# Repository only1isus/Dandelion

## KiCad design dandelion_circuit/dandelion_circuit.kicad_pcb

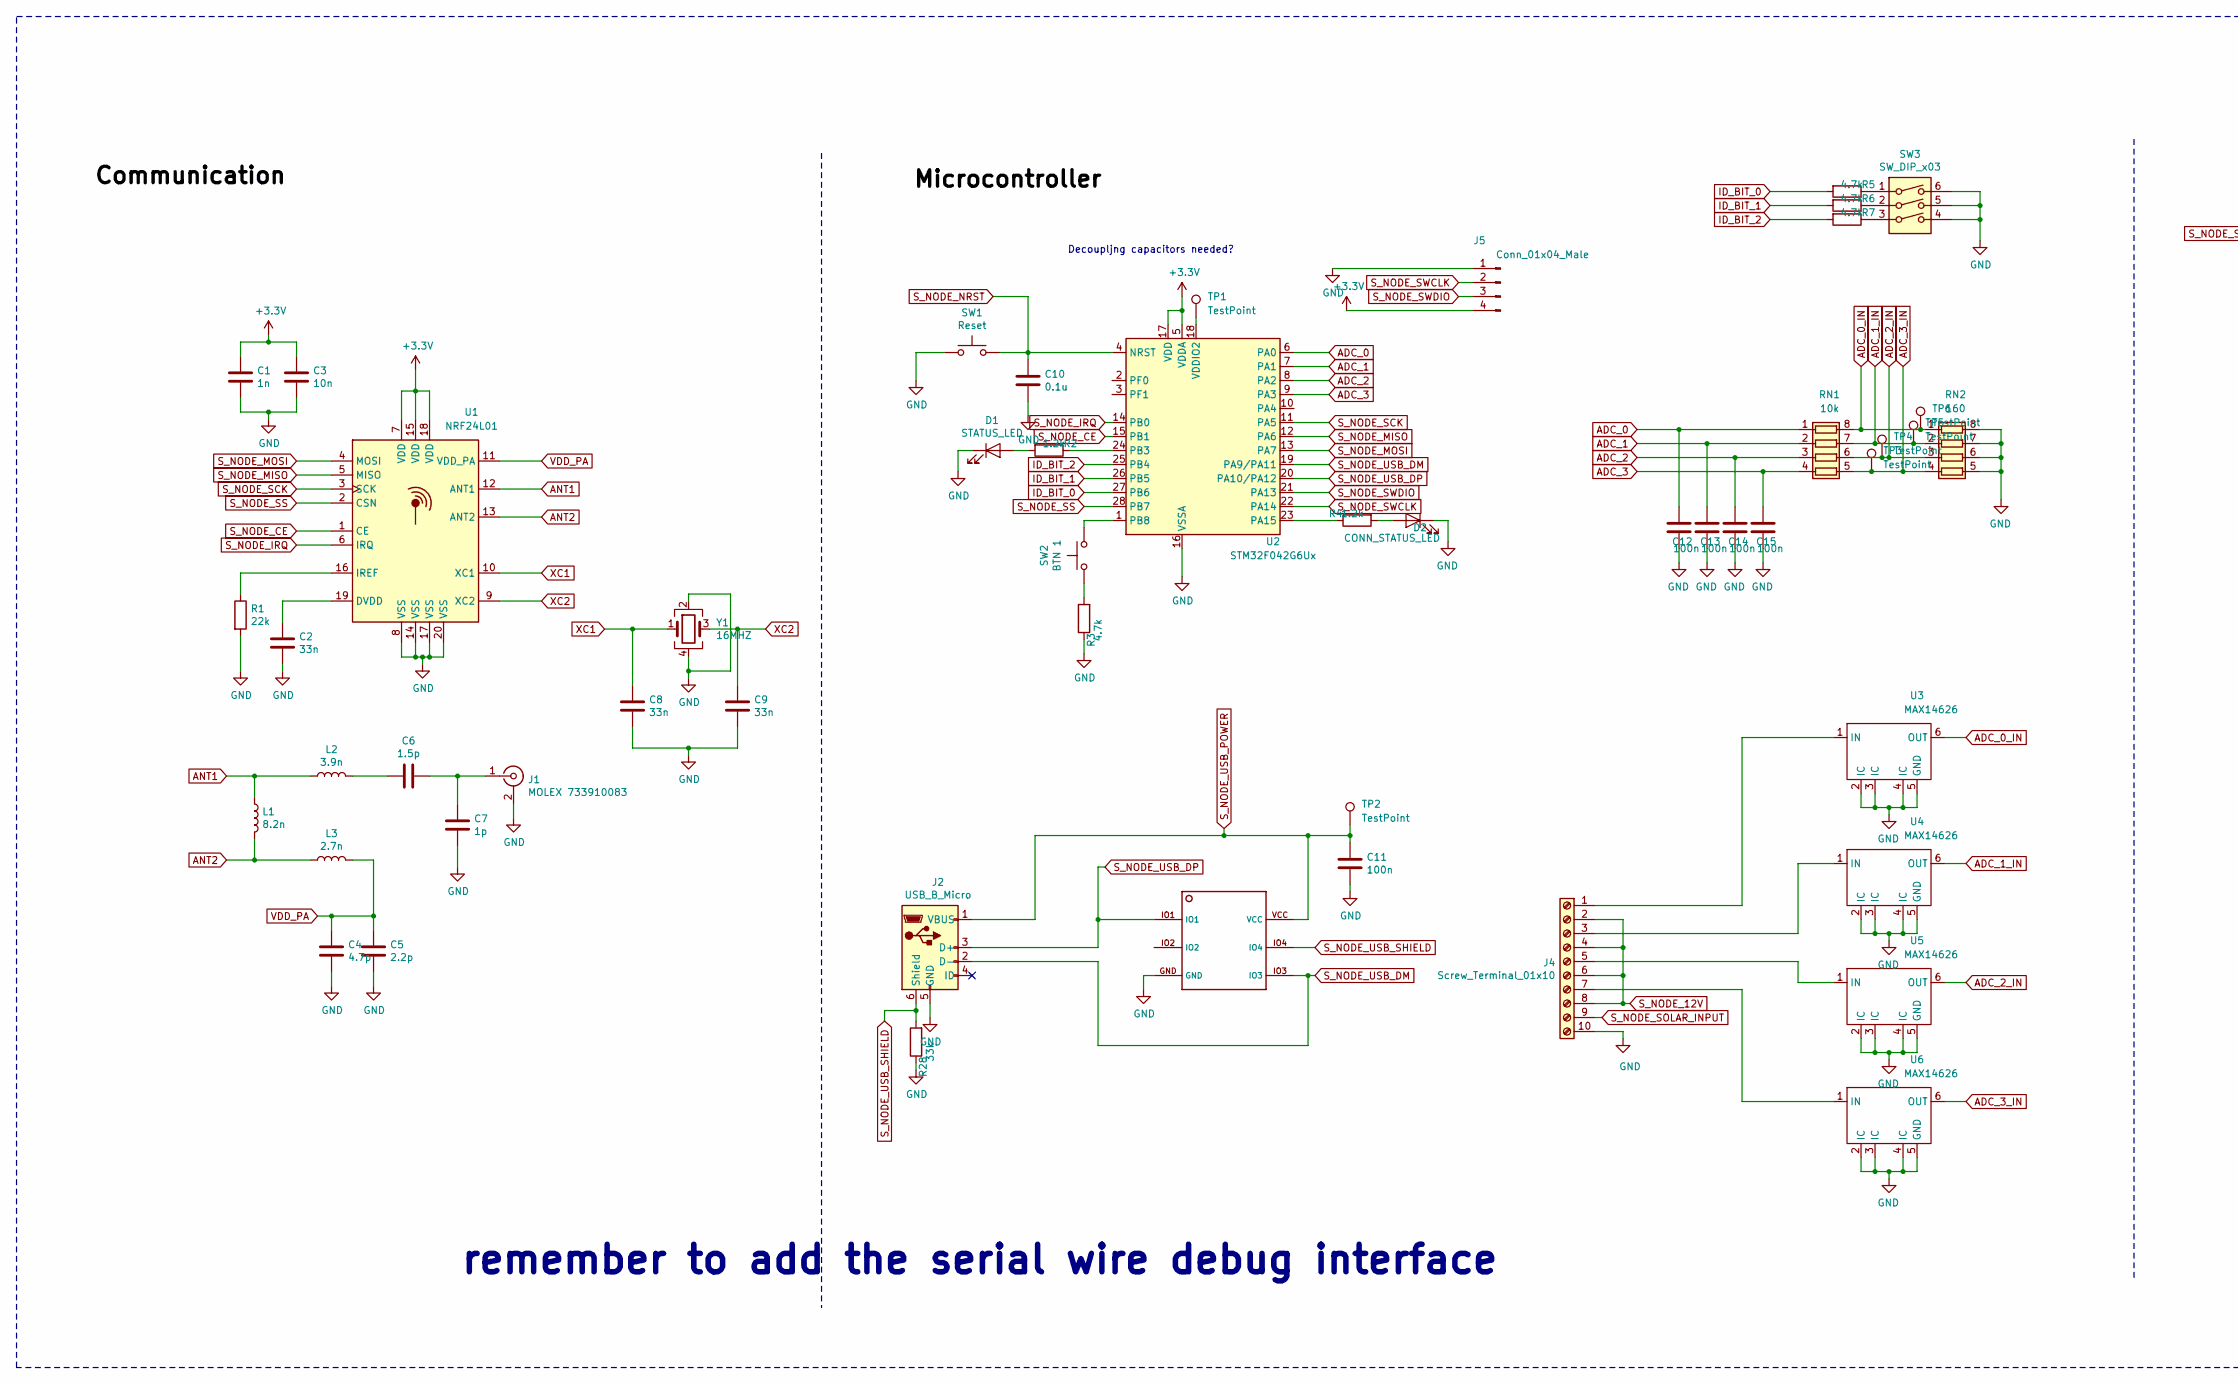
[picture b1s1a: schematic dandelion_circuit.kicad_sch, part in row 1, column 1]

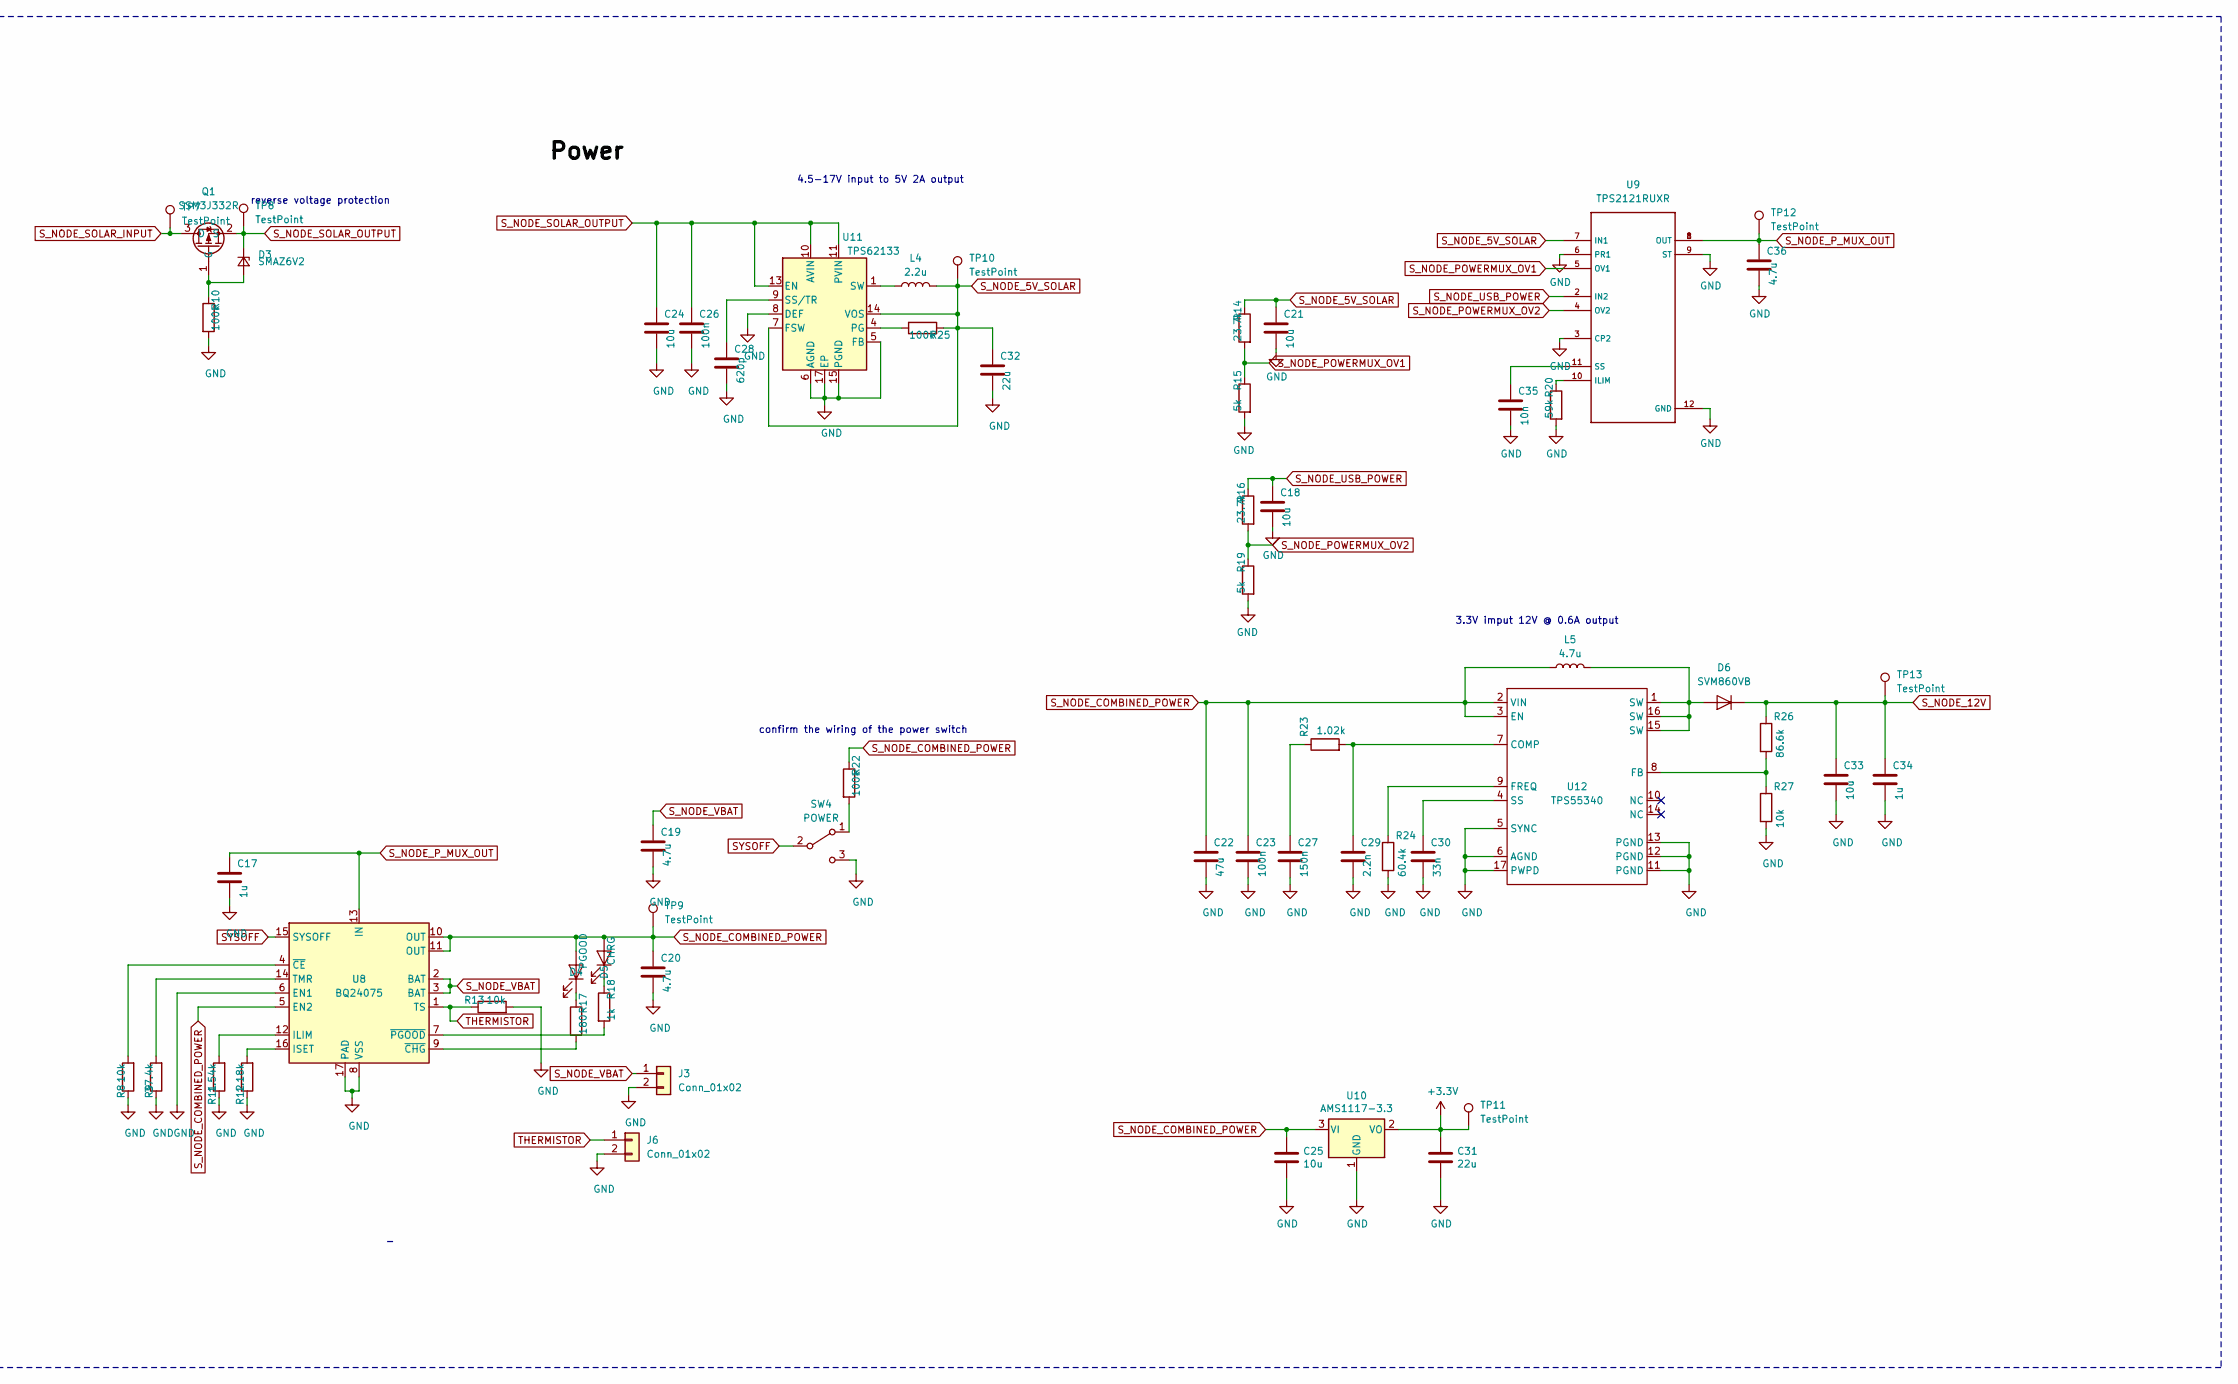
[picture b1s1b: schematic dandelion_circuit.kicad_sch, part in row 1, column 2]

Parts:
C1: 1n; C_0402_1005Metric
C2, C8, C9, C30: 33n; C_0402_1005Metric
C3, C35: 10n; C_0402_1005Metric
C4: 4.7p; C_0402_1005Metric
C5: 2.2p; C_0402_1005Metric
C6: 1.5p; C_0402_1005Metric
C7: 1p; C_0402_1005Metric
C10: 0.1u; C_0402_1005Metric
C11, C12, C13, C14, C15, C23, C26: 100n; C_0402_1005Metric
C17, C34: 1u; C_0402_1005Metric
C18, C24: 10u; C_0805_2012Metric
C19, C20: 4.7u; C_0402_1005Metric
C21, C25, C33: 10u; C_0402_1005Metric
C22: 47u; C_0402_1005Metric
C27: 150n; C_0402_1005Metric
C28: 620p; C_0402_1005Metric
C29: 2.2n; C_0402_1005Metric
C31, C32: 22u; C_0402_1005Metric
C36: 4.7u; C_0805_2012Metric
D1: STATUS_LED; LED_0805_2012Metric
D2: CONN_STATUS_LED; LED_0805_2012Metric
D3: SMAZ6V2; D_SMA
D4: PGOOD; LED_0805_2012Metric
D5: CHRG; LED_0805_2012Metric
D6: SVM860VB; TO-277B
J1: MOLEX 733910083; U.FL_Molex_MCRF_73412-0110_Vertical
J2: USB_B_Micro; USB_Micro-B_Molex-105133-0031
J3, J6: Conn_01x02; PinHeader_1x02_P2.00mm_Vertical
J4: Screw_Terminal_01x10; Connector_Phoenix_MKKDSN
J5: Conn_01x04_Male; PinHeader_1x04_P1.27mm_Vertical
L1: 8.2n; L_0402_1005Metric
L2: 3.9n; L_0402_1005Metric
L3: 2.7n; L_0402_1005Metric
L4: 2.2u; Inductor_Sunlord_MWSA0603
L5: 4.7u; Sunlord_MWSA0503S
Q1: SSM3J332R; SOT-23
R1: 22k; R_0402_1005Metric
R2, R4: 1.2k; R_0402_1005Metric
R3, R5, R6, R7: 4.7k; R_0402_1005Metric
R8, R13, R27: 10k; R_0402_1005Metric
R9: 37.4k; R_0402_1005Metric
R10: 100k; R_0603_1608Metric
R11: 1.54k; R_0603_1608Metric
R12: 1.18k; R_0603_1608Metric
R14, R16: 23.7k; R_0402_1005Metric
R15, R19: 5k; R_0402_1005Metric
R17: 180; R_0402_1005Metric
R18: 1k; R_0402_1005Metric
R20: 59k; R_0402_1005Metric
R22, R25: 100k; R_0402_1005Metric
R23: 1.02k; R_0402_1005Metric
R24: 60.4k; R_0402_1005Metric
R26: 86.6k; R_0402_1005Metric
R28: 33k; R_0402_1005Metric
RN1: 10k; R_Array_Convex_4x0603
RN2: 160; R_Array_Convex_4x0603
SW1: Reset; SW_Push_1P1T_NO_Vertical_Wuerth_434133025816
SW2: BTN 1; SW_Push_1P1T_NO_Vertical_Wuerth_434133025816
SW3: SW_DIP_x03; SW_DIP_SPSTx03_Slide_KingTek_DSHP03TJ_W5.25mm_P1.27mm_JPin
SW4: POWER; SW_SPDT_PCM12
TP1, TP2, TP3, TP4, TP5, TP6, TP7, TP8, TP9, TP10, TP11, TP12, TP13: TestPoint; TestPoint_Pad_2.0x2.0mm
U1: NRF24L01; QFN-20-1EP_4x4mm_P0.5mm_EP2.5x2.5mm
U2: STM32F042G6Ux; QFN-28_4x4mm_P0.5mm
U3, U4, U5, U6: MAX14626; DFN-6-1EP_3x3mm_P1mm_EP1.5x2.4mm
U8: BQ24075; VQFN-16-1EP_3x3mm_P0.5mm_EP1.68x1.68mm_ThermalVias
U9: TPS2121RUXR; IC_TPS2121RUXR
U10: AMS1117-3.3; SOT-223-3_TabPin2
U11: TPS62133; VQFN-16-1EP_3x3mm_P0.5mm_EP1.68x1.68mm_ThermalVias
U12: TPS55340; QFN50P300X300X80-17N
U13: TPD4E004DRYR; SON-6
Y1: 16MHZ; Crystal_SMD_Abracon_ABM10-4Pin_2.5x2.0mm

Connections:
+3V3: C1.1, C3.1, C31.1, J5.4, TP11.1, U1.7 (VDD), U1.15 (VDD), U1.18 (VDD), U2.5 (VDDA), U2.17 (VDD), U10.2 (VO)
ADC_0: C12.1, RN1.1 (R1.1), U2.6 (PA0)
ADC_0_IN: RN1.8 (R1.2), RN2.1 (R1.1), TP6.1, U3.6 (OUT)
ADC_1: C13.1, RN1.2 (R2.1), U2.7 (PA1)
ADC_1_IN: RN1.7 (R2.2), RN2.2 (R2.1), TP5.1, U4.6 (OUT)
ADC_2: C14.1, RN1.3 (R3.1), U2.8 (PA2)
ADC_2_IN: RN1.6 (R3.2), RN2.3 (R3.1), TP4.1, U5.6 (OUT)
ADC_3: C15.1, RN1.4 (R4.1), U2.9 (PA3)
ADC_3_IN: RN1.5 (R4.2), RN2.4 (R4.1), TP3.1, U6.6 (OUT)
ANT1: L1.1, L2.1, U1.12 (ANT1)
ANT2: L1.2, L3.1, U1.13 (ANT2)
GND: C1.2, C2.2, C3.2, C4.2, C5.2, C7.2, C8.2, C9.2, C10.2, C11.2, C12.2, C13.2, C14.2, C15.2, C17.2, C18.2, C19.2, C20.2, C21.2, C22.2, C23.2, C24.2, C25.2, C26.2, C27.2, C28.2, C29.2, C30.2, C31.2, C32.2, C33.2, C34.2, C35.2, C36.2, D1.1 (K), D2.1 (K), J1.2 (Ext), J2.5 (GND), J3.2, J4.10, J5.1, J6.2, R1.2, R3.1, R8.1, R9.1, R10.2, R11.1, R12.1, R13.2, R15.2, R19.2, R20.2, R24.2, R27.2, R28.1, RN2.5 (R4.2), RN2.6 (R3.2), RN2.7 (R2.2), RN2.8 (R1.2), SW1.1, SW3.4, SW3.5, SW3.6, SW4.3 (C), U1.8 (VSS), U1.14 (VSS), U1.17 (VSS), U1.20 (VSS), U2.16 (VSSA), U3.2 (IC), U3.3 (IC), U3.4 (IC), U3.5 (GND), U4.2 (IC), U4.3 (IC), U4.4 (IC), U4.5 (GND), U5.2 (IC), U5.3 (IC), U5.4 (IC), U5.5 (GND), U6.2 (IC), U6.3 (IC), U6.4 (IC), U6.5 (GND), U8.6 (EN1), U8.8 (VSS), U8.17 (PAD), U9.3 (CP2), U9.6 (PR1), U9.9 (ST), U9.12 (GND), U10.1 (GND), U11.5 (FB), U11.6 (AGND), U11.8 (DEF), U11.15 (PGND), U11.16 (PGND), U11.17 (EP), U12.5 (SYNC), U12.6 (AGND), U12.11 (PGND), U12.12 (PGND), U12.13 (PGND), U12.17 (PWPD), U13.GND, Y1.2, Y1.4
ID_BIT_0: R5.2, U2.27 (PB6)
ID_BIT_1: R6.2, U2.26 (PB5)
ID_BIT_2: R7.2, U2.25 (PB4)
unnamed: C2.1, U1.19 (DVDD)
unnamed: C6.1, L2.2
unnamed: C6.2, C7.1, J1.1 (In)
unnamed: C27.1, R23.1
unnamed: C28.1, U11.9 (SS/TR)
unnamed: C29.1, R23.2, U12.7 (COMP)
unnamed: C30.1, U12.4 (SS)
unnamed: C35.1, U9.11 (SS)
unnamed: D1.2 (A), R2.2
unnamed: D2.2 (A), R4.2
unnamed: D3.2 (A), Q1.1 (G), R10.1
unnamed: D4.1 (K), R17.1
unnamed: D5.1 (K), R18.1
unnamed: D6.2 (A), L5.2, U12.1 (SW), U12.15 (SW), U12.16 (SW)
unnamed: J4.1, U3.1 (IN)
unnamed: J4.3, U4.1 (IN)
unnamed: J4.5, U5.1 (IN)
unnamed: J4.7, U6.1 (IN)
unnamed: L4.2, U11.1 (SW), U11.2 (SW), U11.3 (SW)
unnamed: R1.1, U1.16 (IREF)
unnamed: R2.1, U2.24 (PB3)
unnamed: R3.2, SW2.2
unnamed: R4.1, U2.23 (PA15)
unnamed: R5.1, SW3.1
unnamed: R6.1, SW3.2
unnamed: R7.1, SW3.3
unnamed: R8.2, U8.4 (~CE)
unnamed: R9.2, U8.14 (TMR)
unnamed: R11.2, U8.12 (ILIM)
unnamed: R12.2, U8.16 (ISET)
unnamed: R17.2, U8.9 (~CHG)
unnamed: R18.2, U8.7 (~PGOOD)
unnamed: R20.1, U9.10 (ILIM)
unnamed: R22.2, SW4.1 (A)
unnamed: R24.1, U12.9 (FREQ)
unnamed: R25.2, U11.4 (PG)
unnamed: R26.2, R27.1, U12.8 (FB)
unnamed: SW2.1, U2.1 (PB8)
unnamed: TP1.1, U2.18 (VDDIO2)
SYSOFF: SW4.2 (B), U8.15 (SYSOFF)
S_NODE_5V_SOLAR: C21.1, C32.1, L4.1, R14.1, R25.1, TP10.1, U9.7 (IN1), U11.7 (FSW), U11.14 (VOS)
S_NODE_12V: C33.1, C34.1, D6.1 (K), J4.2, J4.4, J4.6, J4.8, R26.1, TP13.1
S_NODE_CE: U1.1 (CE), U2.15 (PB1)
S_NODE_COMBINED_POWER: C20.1, C22.1, C23.1, C25.1, D4.2 (A), D5.2 (A), L5.1, R22.1, TP9.1, U8.5 (EN2), U8.10 (OUT), U8.11 (OUT), U10.3 (VI), U12.2 (VIN), U12.3 (EN)
S_NODE_IRQ: U1.6 (IRQ), U2.14 (PB0)
S_NODE_MISO: U1.5 (MISO), U2.12 (PA6)
S_NODE_MOSI: U1.4 (MOSI), U2.13 (PA7)
S_NODE_NRST: C10.1, SW1.2, U2.4 (NRST)
S_NODE_POWERMUX_OV1: R14.2, R15.1, U9.5 (OV1)
S_NODE_POWERMUX_OV2: R16.2, R19.1, U9.4 (OV2)
S_NODE_P_MUX_OUT: C17.1, C36.1, TP12.1, U8.13 (IN), U9.1 (OUT), U9.8 (OUT)
S_NODE_SCK: U1.3 (SCK), U2.11 (PA5)
S_NODE_SOLAR_INPUT: J4.9, Q1.3 (D), TP7.1
S_NODE_SOLAR_OUTPUT: C24.1, C26.1, D3.1 (K), Q1.2 (S), TP8.1, U11.10 (AVIN), U11.11 (PVIN), U11.12 (PVIN), U11.13 (EN)
S_NODE_SS: U1.2 (CSN), U2.28 (PB7)
S_NODE_SWCLK: J5.2, U2.22 (PA14)
S_NODE_SWDIO: J5.3, U2.21 (PA13)
S_NODE_USB_DM: J2.2 (D-), U2.19 (PA9/PA11), U13.IO3
S_NODE_USB_DP: J2.3 (D+), U2.20 (PA10/PA12), U13.IO1
S_NODE_USB_POWER: C11.1, C18.1, J2.1 (VBUS), R16.1, TP2.1, U9.2 (IN2), U13.VCC
S_NODE_USB_SHIELD: J2.6 (Shield), R28.2, U13.IO4
S_NODE_VBAT: C19.1, J3.1, U8.2 (BAT), U8.3 (BAT)
THERMISTOR: J6.1, R13.1, U8.1 (TS)
VDD_PA: C4.1, C5.1, L3.2, U1.11 (VDD_PA)
XC1: C8.1, U1.10 (XC1), Y1.1
XC2: C9.1, U1.9 (XC2), Y1.3

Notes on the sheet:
Decoupljng capacitors needed?
remember to add the serial wire debug interface
reverse voltage protection
4.5-17V input to 5V 2A output
confirm the wiring of the power switch
3.3V imput 12V @ 0.6A output

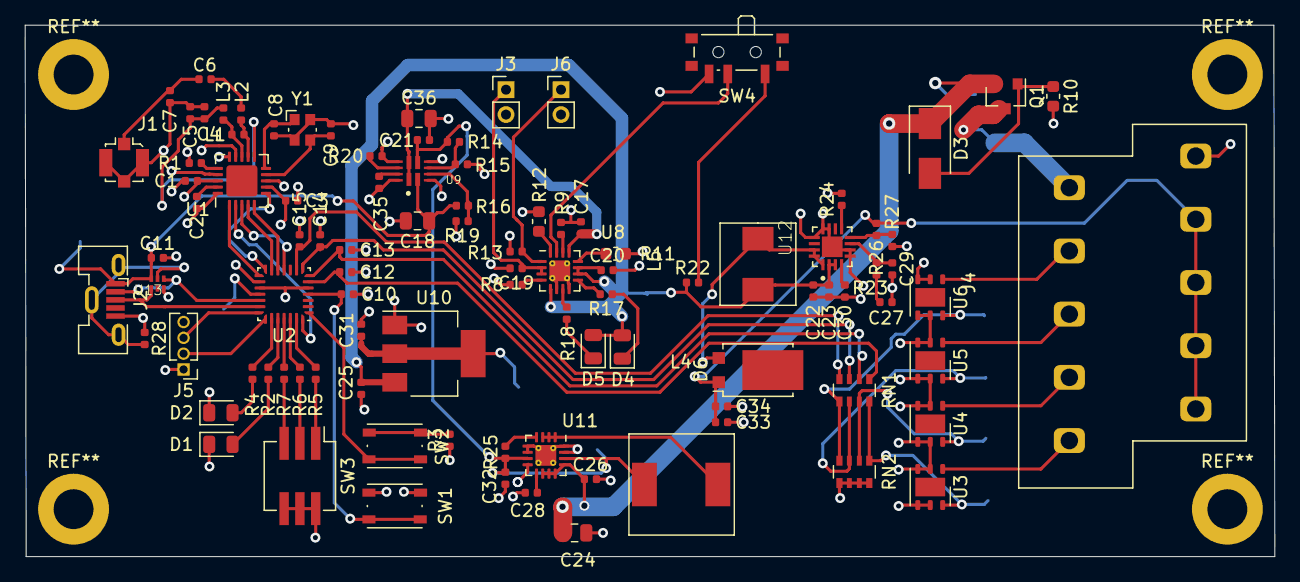
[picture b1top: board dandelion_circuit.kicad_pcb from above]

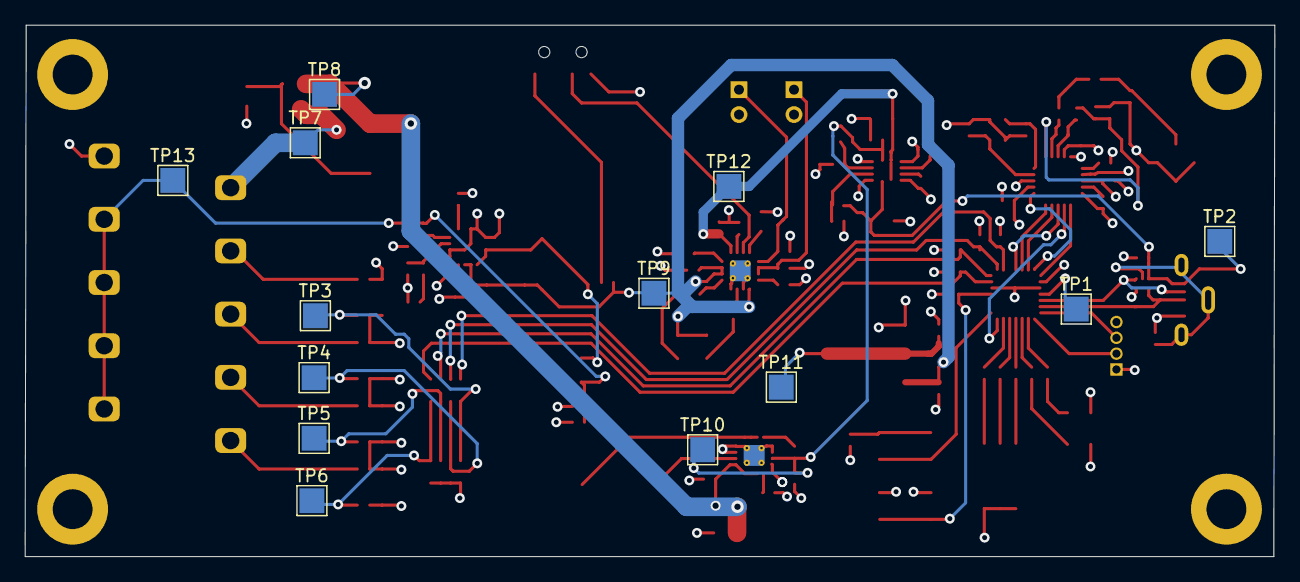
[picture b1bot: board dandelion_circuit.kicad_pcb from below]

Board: 4 copper layers, 100.4 x 42.7 mm, 112 parts (13 on the bottom side), 81 nets.

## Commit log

2020-05-28 under heavy construction
2020-06-20 removed undervoltage protection and added power mux ic to handle solar and USB input
2020-07-03 Final circuit design
2020-07-17 Finished all the routing for SLAVE NODE
